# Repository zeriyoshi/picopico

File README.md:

# picopico EVT (Engineering Validation Test)

Validation and production test of `zeriyoshi/picoletta` and `zeriyoshi/xtrapico`.

## Specs

- Two `RP2040` implementations
    - BIG: Based on [`RetroScaler/RP2040-PICO-BOOT`](https://github.com/RetroScaler/RP2040-PICO-BOOT)
        - For main keyboard controller
        - Better and Rich implementation, not optimized usecase.
    - little: Based on [`zeriyoshi/xtrapico`](https://github.com/zeriyoshi/xtrapico)
        - For Raspberry Pi Pico compatible module
        - Simple and Flexible implementation, but unsure if it works.
        - xtrapico based on [`Breadstick-Innovations/22008-RP2040-Dev-Board`](https://github.com/Breadstick-Innovations/22008-RP2040-Dev-Board)
- `WS2812B-V5` and `SK6182MINI` testing environments
    - `RP2040` -> `WS2812B-V5` -> `SK6182MINI` Voltage conversion
    - `RP2040` -> MOSFET -> `SK6182MINI` Voltage conversion
    - Direct drive `SK6182MINI` on 3.3V
- Focus on manufactualing by [JLCPCB](https://jlcpcb.com/)

## Requirements

- KiCad 7
    - [`Bouni/kicad-jlcpcb-tools`](https://github.com/Bouni/kicad-jlcpcb-tools)
- Python 3
- Java Runtime Environment (for [`freerouting/freerouting`](https://github.com/freerouting/freerouting))

```bash
$ git clone --recursive "https://github.com/zeriyoshi/picopico" "picopico"
$ cd "picopico"
$ pip install -r "requirements.txt"
```

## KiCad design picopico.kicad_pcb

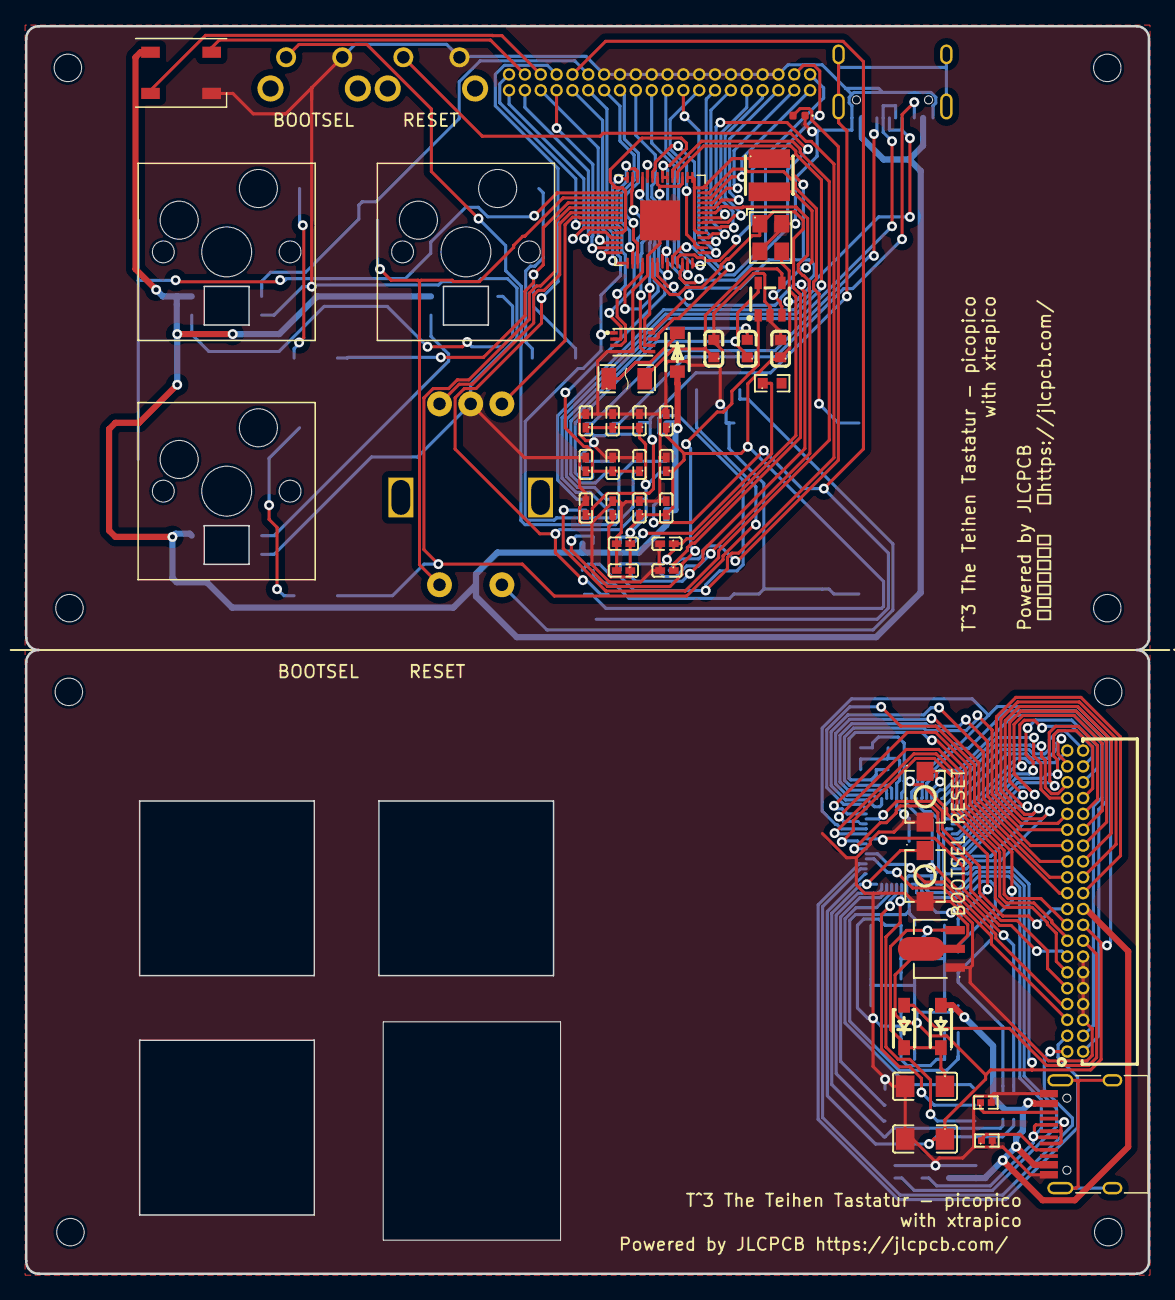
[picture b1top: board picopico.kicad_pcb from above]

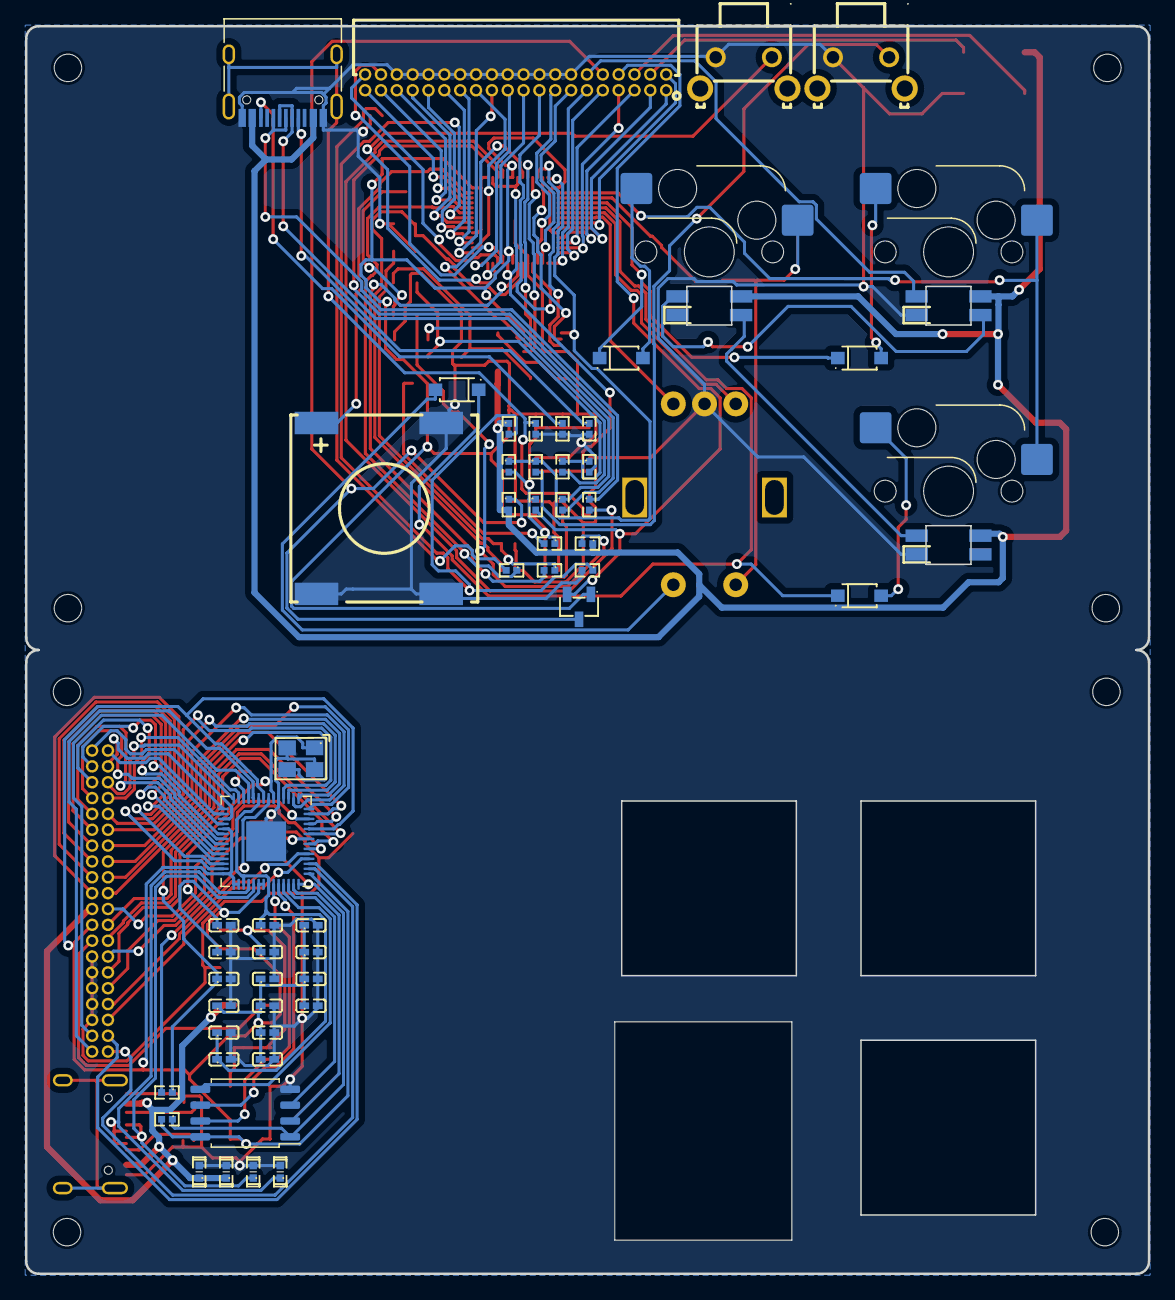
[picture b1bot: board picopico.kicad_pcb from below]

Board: 2 copper layers, 90.0 x 100.0 mm, 113 parts (55 on the bottom side), 124 nets.

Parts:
C1, C5, C6, C11, C12, C14, C15, C16, C17, C18, C19: CL05B104KO5NNNC; C0402
C2, C4: CL10A106KP8NNNC; C0603
C3: CL10C220JB8NNNC; C0603
C7: CL05A106MQ5NUNC; C0402
C8, C9: 0402CG220J500NT; C0402
C10, C13: CL05A105KA5NQNC; C0402
D1: WS2812B; LED_WS2812B_PLCC4_5.0x5.0mm_P3.2mm
D2: LED; LED_0402_1005Metric
D3, D4, D5, D6: 0402ESDA-05N; D0402-BI
F1: nSMD050-24V; F1206
FLASH1: W25Q16JVUXIQ; USON-8_L3.0-W2.0-P0.50-BL-EP
G2, G2#2: LOGO; zeriparrot
H1, H2, H3, H4, H5, H6, H7, H8: MountingHole; MountingHole_2.2mm_M2
H9, H10, H11: Switch_Hole
H12: RotaryEncoder_EC11-Hole
J1, J2: USB_C_Receptacle_USB2.0_14P; USB_C_Receptacle_HRO_TYPE-C-31-M-12
L1: SWPA3015S2R2NT; IND-SMD_L3.0-W3.0
R1, R2, R19, R20: 0402WGF5101TCE; R0402
R3: 0402WGF220JTCE; R0402
R4: 0402WGF5601TCE; R0402
R5, R10, R12, R16, R17: 0402WGF1002TCE; R0402
R6: 0402WGF1003TCE; R0402
R7: 0402WGF1503TCE; R0402
R8: 0402WGF6803TCE; R0402
R9, R11: 0402WGF1001TCE; R0402
R13: 0603WAF2001T5E; R0603
R14, R15: RC0402FR-0727RL; R0402
R18: 0402WGF4701TCE; R0402
SW1, SW2, SW3: SW_PUSH; SW_Hotswap_Kailh_MX_1.00u
SW4: RotaryEncoder_EC11-Switch
SW5, SW6: TSA343G00-250J2; SW-SMD_L4.0-W2.9-LS5.0
SW_BOOTSEL1: 1-1825027-7; SW-TH_KH-6X6X4.3H-ZJ
SW_RESET1: 1-1825027-7; SW-TH_KH-6X6X4.3H-ZJ
U1: 1N4002W; SOD-123F_L2.8-W1.8-LS3.7-RD
U2: TD6810; SOT-23-5_L3.0-W1.7-P0.95-LS2.8-BR
U3: RP2040; QFN-56-1EP_7x7mm_P0.4mm_EP3.2x3.2mm
U4, U14: X1321FR-2X20-C43D24; CONN-TH_40P_X1321FR-2X20-C43D24
U5, U6, U7, U8: 1N4148W_C81598; SOD-123F_L2.7-W1.6-LS3.8-RD
U9: BSS138; SOT-23-3_L2.9-W1.3-P1.90-LS2.4-BR
U10, U11, U12: RGBLED_SK6812MINI-E
U13: FS-1540; BUZ-SMD_5P-L15.0-W15.0-P13.7-BL
X1: X322512MSB4SI; OSC-SMD_4P-L3.2-W2.5-BL
XTRAPI_C1, XTRAPI_C3: 0402CG300J500NT; C0402
XTRAPI_C2, XTRAPI_C5, XTRAPI_C6, XTRAPI_C7, XTRAPI_C8, XTRAPI_C9, XTRAPI_C10, XTRAPI_C11, XTRAPI_C12, XTRAPI_C13, XTRAPI_C15, XTRAPI_C16, XTRAPI_C17, XTRAPI_C18: CL05A106MQ5NUNC; C0402
XTRAPI_C4, XTRAPI_C14: CL31A107MQHNNNE; C1206
XTRAPI_R2: 0402WGF1002TCE; R0402
XTRAPI_R4: 0402WGF1001TCE; R0402
XTRAPI_U2: W25Q128JVS; SOIC-8_5.23x5.23mm_P1.27mm
XTRAPI_U3: RP2040; QFN-56-1EP_7x7mm_P0.4mm_EP3.2x3.2mm
XTRAPI_U4: AZ1117R-3_3TRE1; SOT-89-3_L4.5-W2.5-P1.50-LS4.2-BR
XTRAPI_U6, XTRAPI_U7: B5819W_C8598; SOD-123_L2.7-W1.6-LS3.7-RD-1
XTRAPI_X1: X322512MSB4SI; OSC-SMD_4P-L3.2-W2.5-BL

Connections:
+1V1: C10.1, C11.1, C12.1, U3.23 (DVDD), U3.45 (VREG_VOUT), U3.50 (DVDD)
+3V3: C4.1, C5.1, C6.1, C7.1, C13.1, C14.1, C15.1, C16.1, C17.1, C18.1, C19.1, FLASH1.8 (VCC), L1.2, R10.2, R12.1, R16.1, U3.1 (IOVDD), U3.10 (IOVDD), U3.22 (IOVDD), U3.33 (IOVDD), U3.42 (IOVDD), U3.43 (ADC_AVDD), U3.44 (VREG_IN), U3.48 (USB_VDD), U3.49 (IOVDD), U9.1 (G)
/COL0: SW1.1, SW3.1, U3.2 (GPIO0)
/COL1: SW2.1, SW4.S2, U3.3 (GPIO1)
/GPIO24: R4.2, R5.1, U3.36 (GPIO24)
/GPIO25: R18.1, U3.37 (GPIO25)
/MOSFETIN: R16.2, U4.8, U9.2 (S)
/MOSFETOUT: R17.1, U4.10, U9.3 (D)
/RGBEXT: U3.8 (GPIO6), U4.2
/RGBREV: U4.12, U10.4 (DIN)
/ROT0IN: SW4.B, U3.6 (GPIO4)
/ROT0OUT: SW4.A, U3.7 (GPIO5)
/ROW0: U3.4 (GPIO2), U5.1 (K), U6.1 (K)
/ROW1: U3.5 (GPIO3), U7.1 (K), U8.1 (K)
/SWCLK: U3.24 (SWCLK), U4.38
/SWD: U3.25 (SWD), U4.40
/VSYS: F1.1, U1.1 (C)
/WSIN: D1.4 (DIN), U4.4
/WSOUT: D1.2 (DOUT), U4.6
/XP_+3V3: U14.18, XTRAPI_C2.1, XTRAPI_C4.1, XTRAPI_C5.1, XTRAPI_C10.1, XTRAPI_C11.1, XTRAPI_C12.1, XTRAPI_C13.1, XTRAPI_C15.1, XTRAPI_C16.1, XTRAPI_C17.1, XTRAPI_C18.1, XTRAPI_R2.2, XTRAPI_U2.8 (VCC), XTRAPI_U3.1 (IOVDD), XTRAPI_U3.10 (IOVDD), XTRAPI_U3.22 (IOVDD), XTRAPI_U3.33 (IOVDD), XTRAPI_U3.42 (IOVDD), XTRAPI_U3.43 (ADC_AVDD), XTRAPI_U3.44 (VREG_IN), XTRAPI_U3.48 (USB_VDD), XTRAPI_U3.49 (IOVDD), XTRAPI_U4.2 (OUTPUT)
/XP_BOOTSEL: SW6.1, XTRAPI_R2.1, XTRAPI_U2.1 (~CS), XTRAPI_U3.56 (QSPI_SS)
/XP_GPIO0: U14.1, XTRAPI_U3.2 (GPIO0)
/XP_GPIO1: U14.3, XTRAPI_U3.3 (GPIO1)
/XP_GPIO2: U14.5, XTRAPI_U3.4 (GPIO2)
/XP_GPIO3: U14.7, XTRAPI_U3.5 (GPIO3)
/XP_GPIO4: U14.9, XTRAPI_U3.6 (GPIO4)
/XP_GPIO5: U14.11, XTRAPI_U3.7 (GPIO5)
/XP_GPIO6: U14.13, XTRAPI_U3.8 (GPIO6)
/XP_GPIO7: U14.15, XTRAPI_U3.9 (GPIO7)
/XP_GPIO8: U14.17, XTRAPI_U3.11 (GPIO8)
/XP_GPIO9: U14.19, XTRAPI_U3.12 (GPIO9)
/XP_GPIO10: U14.21, XTRAPI_U3.13 (GPIO10)
/XP_GPIO11: U14.23, XTRAPI_U3.14 (GPIO11)
/XP_GPIO12: U14.25, XTRAPI_U3.15 (GPIO12)
/XP_GPIO13: U14.27, XTRAPI_U3.16 (GPIO13)
/XP_GPIO14: U14.29, XTRAPI_U3.17 (GPIO14)
/XP_GPIO15: U14.31, XTRAPI_U3.18 (GPIO15)
/XP_GPIO16: U14.33, XTRAPI_U3.27 (GPIO16)
/XP_GPIO17: U14.35, XTRAPI_U3.28 (GPIO17)
/XP_GPIO18: U14.37, XTRAPI_U3.29 (GPIO18)
/XP_GPIO19: U14.39, XTRAPI_U3.30 (GPIO19)
/XP_GPIO20: U14.40, XTRAPI_U3.31 (GPIO20)
/XP_GPIO21: U14.38, XTRAPI_U3.32 (GPIO21)
/XP_GPIO22: U14.36, XTRAPI_U3.34 (GPIO22)
/XP_GPIO23: U14.34, XTRAPI_U3.35 (GPIO23)
/XP_GPIO24: U14.32, XTRAPI_U3.36 (GPIO24)
/XP_GPIO25: U14.30, XTRAPI_U3.37 (GPIO25)
/XP_GPIO26_ADC0: U14.28, XTRAPI_U3.38 (GPIO26_ADC0)
/XP_GPIO27_ADC1: U14.26, XTRAPI_U3.39 (GPIO27_ADC1)
/XP_GPIO28_ADC2: U14.24, XTRAPI_U3.40 (GPIO28_ADC2)
/XP_GPIO29_ADC3: U14.22, XTRAPI_U3.41 (GPIO29_ADC3)
/XP_RUN: SW5.1, XTRAPI_U3.26 (RUN)
/XP_SWCLK: U14.2, XTRAPI_U3.24 (SWCLK)
/XP_SWD: U14.4, XTRAPI_U3.25 (SWD)
/XP_USB_DN: D6.1, J2.A7 (D-), J2.B7 (D-), XTRAPI_U3.46 (USB_DM)
/XP_USB_DP: D5.1, J2.A6 (D+), J2.B6 (D+), XTRAPI_U3.47 (USB_DP)
/XP_VBUS: D3.1, D4.1, J2.A4 (VBUS), J2.A9 (VBUS), J2.B4 (VBUS), J2.B9 (VBUS), U14.20, XTRAPI_U7.2 (+)
/XP_VSYS: U14.16, XTRAPI_U6.2 (+)
GND: C1.2, C2.2, C4.2, C5.2, C6.2, C7.2, C8.2, C9.2, C10.2, C11.2, C12.2, C13.2, C14.2, C15.2, C16.2, C17.2, C18.2, C19.2, D1.3 (VSS), D2.1 (K), D3.2, D4.2, D5.2, D6.2, FLASH1.4 (GND), FLASH1.9 (EP), J1.A1 (GND), J1.A12 (GND), J1.B1 (GND), J1.B12 (GND), J2.A1 (GND), J2.A12 (GND), J2.B1 (GND), J2.B12 (GND), R1.2, R2.2, R3.2, R5.2, R7.2, R19.2, R20.2, SW4.C, SW5.2, SW6.2, SW_BOOTSEL1.2, SW_RESET1.2, U2.2 (GND), U3.19 (TESTEN), U3.57 (GND), U4.14, U4.16, U4.18, U4.20, U4.22, U4.24, U4.26, U4.28, U4.30, U4.32, U4.34, U4.36, U10.3 (GND), U11.3 (GND), U12.3 (GND), U13.2, U13.3, U13.4, U14.6, U14.8, U14.10, U14.12, U14.14, X1.2 (GND), X1.4 (GND), XTRAPI_C1.2, XTRAPI_C2.2, XTRAPI_C3.2, XTRAPI_C4.2, XTRAPI_C5.2, XTRAPI_C6.2, XTRAPI_C7.2, XTRAPI_C8.2, XTRAPI_C9.2, XTRAPI_C10.2, XTRAPI_C11.2, XTRAPI_C12.2, XTRAPI_C13.2, XTRAPI_C14.2, XTRAPI_C15.2, XTRAPI_C16.2, XTRAPI_C17.2, XTRAPI_C18.2, XTRAPI_U2.4 (GND), XTRAPI_U3.19 (TESTEN), XTRAPI_U3.57 (GND), XTRAPI_U4.1 (ADJ/GND), XTRAPI_X1.2 (GND), XTRAPI_X1.4 (GND)
unnamed: C3.2, R8.2
unnamed: D2.2 (A), R18.2
unnamed: FLASH1.6 (CLK), U3.52 (QSPI_SCLK)
unnamed: FLASH1.1 (CS#), R9.1, R10.1, U3.56 (QSPI_SS)
unnamed: FLASH1.5 (DI(IO0)), U3.53 (QSPI_SD0)
unnamed: FLASH1.2 (DO(IO1)), U3.55 (QSPI_SD1)
unnamed: FLASH1.7 (HOLD#orRESET#(IO3)), U3.51 (QSPI_SD3)
unnamed: FLASH1.3 (WP#(IO2)), U3.54 (QSPI_SD2)
unnamed: J1.A5 (CC1), R1.1
unnamed: J1.B5 (CC2), R2.1
unnamed: J1.A6 (D+), J1.B6 (D+), R14.1
unnamed: J1.A7 (D-), J1.B7 (D-), R15.1
unnamed: C1.1, J1.S1 (SHIELD), R3.1
unnamed: J2.A5 (CC1), R20.1
unnamed: J2.B5 (CC2), R19.1
unnamed: R9.2, SW_BOOTSEL1.1
unnamed: R12.2, R13.1
unnamed: R6.2, U2.1 (RUN)
unnamed: L1.1, U2.3 (SW)
unnamed: C3.1, R7.1, R8.1, U2.5 (VFB/VOUT)
unnamed: C2.1, F1.2, U2.4 (VIN)
unnamed: U3.9 (GPIO7), U4.1
unnamed: U3.11 (GPIO8), U4.3
unnamed: U3.12 (GPIO9), U4.5
unnamed: U3.13 (GPIO10), U4.7
unnamed: U3.14 (GPIO11), U4.9
unnamed: U3.15 (GPIO12), U4.11
unnamed: U3.16 (GPIO13), U4.13
unnamed: U3.17 (GPIO14), U4.15
unnamed: U3.18 (GPIO15), U4.17
unnamed: U3.27 (GPIO16), U4.19
unnamed: U3.28 (GPIO17), U4.21
unnamed: U3.29 (GPIO18), U4.23
unnamed: U3.30 (GPIO19), U4.25
unnamed: U3.31 (GPIO20), U4.27
unnamed: U3.32 (GPIO21), U4.29
unnamed: U3.34 (GPIO22), U4.31
unnamed: U3.35 (GPIO23), U4.33
unnamed: U3.38 (GPIO26_ADC0), U4.35
unnamed: U3.39 (GPIO27_ADC1), U4.37
unnamed: U3.40 (GPIO28_ADC2), U4.39
unnamed: SW_RESET1.1, U3.26 (RUN)
unnamed: R15.2, U3.46 (USB_DM)
unnamed: R14.2, U3.47 (USB_DP)
unnamed: C8.1, U3.20 (XIN), X1.1 (OSC1)
unnamed: R11.2, U3.21 (XOUT)
unnamed: SW1.2, U5.2 (A)
unnamed: SW2.2, U6.2 (A)
unnamed: SW3.2, U7.2 (A)
unnamed: SW4.S1, U8.2 (A)
unnamed: U10.2 (DOUT), U11.4 (DIN)
unnamed: U11.2 (DOUT), U12.4 (DIN)
unnamed: U3.41 (GPIO29_ADC3), U13.1 (+)
unnamed: C9.1, R11.1, X1.3 (OSC2)
unnamed: XTRAPI_U2.6 (CLK), XTRAPI_U3.52 (QSPI_SCLK)
unnamed: XTRAPI_U2.5 (DI(IO0)), XTRAPI_U3.53 (QSPI_SD0)
unnamed: XTRAPI_U2.2 (DO(IO1)), XTRAPI_U3.55 (QSPI_SD1)
unnamed: XTRAPI_U2.3 (IO2), XTRAPI_U3.54 (QSPI_SD2)
unnamed: XTRAPI_U2.7 (IO3), XTRAPI_U3.51 (QSPI_SD3)
unnamed: XTRAPI_C6.1, XTRAPI_C7.1, XTRAPI_C8.1, XTRAPI_U3.23 (DVDD), XTRAPI_U3.45 (VREG_VOUT), XTRAPI_U3.50 (DVDD)
unnamed: XTRAPI_C1.1, XTRAPI_U3.20 (XIN), XTRAPI_X1.1 (OSC1)
unnamed: XTRAPI_R4.2, XTRAPI_U3.21 (XOUT)
unnamed: XTRAPI_C9.1, XTRAPI_C14.1, XTRAPI_U4.3 (INPUT), XTRAPI_U6.1 (-), XTRAPI_U7.1 (-)
unnamed: XTRAPI_C3.1, XTRAPI_R4.1, XTRAPI_X1.3 (OSC2)
VBUS: D1.1 (VDD), J1.A4 (VBUS), J1.A9 (VBUS), J1.B4 (VBUS), J1.B9 (VBUS), R4.1, R6.1, R17.2, U1.2 (A), U10.1 (VDD), U11.1 (VDD), U12.1 (VDD)

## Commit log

2024-02-15 rev1
